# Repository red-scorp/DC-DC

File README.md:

```
 ____  _____   _ ____  _____    _____           _         _   
|    \|     | / |    \|     |  |  _  |___ ___  |_|___ ___| |_ 
|  |  |   --|/ /|  |  |   --|  |   __|  _| . | | | -_|  _|  _|
|____/|_____|_/ |____/|_____|  |__|  |_| |___|_| |___|___|_|  
                                             |___|
```

# DC/DC project

This project is intended to implement some simple multipurpose DC/DC buck and buck-boost converters from easy available components.
This project also features Excel based component values calculator.

I've stared this project to create stable and high quality DC/DC module for my private projects, covering most common usecases:

- Step-down to most common fixed voltages 3.3V, 5V and 12V up to 5A
- Step-up/down from 1.8V-5.5V to 3.3V and 5V up to 3A
- Step-up/down from 2.5V-12V to 3.3V and 5V up to 1A

## DCDC-12V5V5A

**DCDC-12V5V5A** is simple DC/DC step-down converter with fixed output 5V.
When used for more than 1A current it's recommended to glue a heat sink about 20x20mm in a middle of the bottom side of the board.

Preview:

[Schematics in PDF format](doc/DCDC-12V5V5A.pdf)

Features:

- Input: **12V (7V-24V)**
- Output: **5V**
- Current: **5A (peak 10A)**
- Switching: **500kHz**
- Efficiency: **up to 90%**
- Board size: **40x24mm**
- Based on: **Ti LM3150**

CAM files are available.
BoM and PnP files for JLCPCB are available.

## DCDC-12V3V5A

**DCDC-12V3V5A** is simple DC/DC step-down converter with fixed output 3.3V.
When used for more than 1A current it's recommended to glue a heat sink about 20x20mm in a middle of the bottom side of the board.

Preview:

[Schematics in PDF format](doc/DCDC-12V3V5A.pdf)

Features:

- Input: **12V (5V-24V)**
- Output: **3.3V**
- Current: **5A (peak 10A)**
- Switching: **600kHz**
- Efficiency: **up to 90%**
- Board size: **40x24mm**
- Based on: **Ti LM3150**

CAM files are available.
BoM and PnP files for JLCPCB are available.

## DCDC-18V12V5A

**DCDC-18V12V5A** is simple DC/DC step-down converter with fixed output 12V.
When used for more than 1A current it's recommended to glue a heat sink about 20x20mm in a middle of the bottom side of the board.

Preview:

[Schematics in PDF format](doc/DCDC-18V12V5A.pdf)

Features:

- Input: **18V (14V-24V)**
- Output: **12V**
- Current: **5A (peak 10A)**
- Switching: **500kHz**
- Efficiency: **up to 90%**
- Board size: **40x24mm**
- Based on: **Ti LM3150**

CAM files are available.
BoM and PnP files for JLCPCB are available.

## DCDC-18VXV5A

**DCDC-18VXV5A** is simple DC/DC step-down converter with selectable output 2-12V.
When used for more than 1A current it's recommended to glue a heat sink about 20x20mm in a middle of the bottom side of the board.

Preview:

[Schematics in PDF format](doc/DCDC-18VXV5A.pdf)

Features:

- Input: **18V (5V-24V)**
- Output: **2-12V**
- Current: **5A (peak 10A)**
- Switching: **500kHz**
- Efficiency: **up to 90%**
- Board size: **40x24mm**
- Based on: **Ti LM3150**

CAM files are available.
BoM and PnP files for JLCPCB are available.

## DCDC-5V5V3A

**DCDC-5V5V3A** is simple DC/DC step-up/down converter with selectable fixed output 3.3/5V.
When used for more than 1A current it's recommended to glue a heat sink about 20x20mm in a middle of the bottom side of the board.

Preview:

[Schematics in PDF format](doc/DCDC-5V5V3A.pdf)

Features:

- Input: **1.8-5.5V**
- Output: **3.3/5V (select)**
- Current: **3A (peak 5A)**
- Switching: **2.4MHz**
- Efficiency: **up to 90%**
- Board size: **40x24mm**
- Based on: **Ti TPS63020**

CAM files are available.
BoM and PnP files for JLCPCB are available.

## DCDC-5VXV3A

**DCDC-5VXV3A** is simple DC/DC step-up/down converter with selectable output 1.2-5V.
When used for more than 1A current it's recommended to glue a heat sink about 20x20mm in a middle of the bottom side of the board.

Preview:

[Schematics in PDF format](doc/DCDC-5VXV3A.pdf)

Features:

- Input: **1.8-5.5V**
- Output: **1.2-5V**
- Current: **3A (peak 5A)**
- Switching: **2.4MHz**
- Efficiency: **up to 90%**
- Board size: **40x24mm**
- Based on: **Ti TPS63020**

CAM files are available.
BoM and PnP files for JLCPCB are available.

## DCDC-12V5V1A

**DCDC-12V5V1A** is simple DC/DC step-up/down converter with selectable fixed output 3.3/5V.
When used for more than 1A current it's recommended to glue a heat sink about 20x20mm in a middle of the bottom side of the board.

Preview:

[Schematics in PDF format](doc/DCDC-12V5V1A.pdf)

Features:

- Input: **2.5-12V**
- Output: **3.3/5V (select)**
- Current: **1A (peak 2A)**
- Switching: **2.4MHz**
- Efficiency: **up to 90%**
- Board size: **40x24mm**
- Based on: **Ti TPS63060**

CAM files are available.
BoM and PnP files for JLCPCB are available.

## DCDC-BASE-X2A

**DCDC-BASE-X2A** is base board for 2 DC/DC modules with common input and two separate outputs.
When used for more than 1A current it's recommended to glue a heat sinks about 20x20mm in a middle of the bottom side of DCDC boards before soldering them to the base board.

Preview:

[Schematics in PDF format](doc/DCDC-BASE-X2A.pdf)

Features:

- Fits two compatible DCDC modules
- Common/single input
- Two separate outputs
- Compatible with heat sinks up to 24x24mm
- Supports direct and/or hole through soldering of DCDC modules

CAM files are available.

## DCDC-BASE-X2B

**DCDC-BASE-X2B** is base board for 2 DC/DC modules with common input and two separate outputs.
When used for more than 1A current it's recommended to glue a heat sinks about 20x20mm in a middle of the bottom side of DCDC boards before soldering them to the base board.

Preview:

[Schematics in PDF format](doc/DCDC-BASE-X2B.pdf)

Features:

- Fits two compatible DCDC modules
- Common/single input
- Two separate outputs
- Compatible with heat sinks up to 24x24mm
- Supports direct and/or hole through soldering of DCDC modules

CAM files are available.

## DCDC-BOX

**DCDC-BOX** is a enclosure for a single DCDC module, suitable for FDM and SLA 3D printing.

STL file is available.

## DCDC-BOX-X2

**DCDC-BOX-X2** is a enclosure for a X2A and X2B base boards, suitable for FDM and SLA 3D printing.

STL file is available.

## Links

- Interesting paper from Ti [Under the hood of a noninverting buck-boost converter](https://www.ti.com/seclit/ml/slup346/slup346.pdf)
- Product page of [Ti LM3150](https://www.ti.com/product/LM3150)
- Product page of [Ti TPS63020](https://www.ti.com/product/TPS63020)
- Product page of [Ti TPS63060](https://www.ti.com/product/TPS63060)

## How to help

Your contributions as code, resources, or finances are welcome! Please contact me directly via email at andriy.golovnya@gmail.com or through my [GitHub profile](https://github.com/red-scorp).

If you'd like to make a financial contribution, you can donate via [PayPal](http://paypal.me/redscorp) or [Ko-Fi](http://ko-fi.com/redscorp). Your support is greatly appreciated.

Thanks in advance!

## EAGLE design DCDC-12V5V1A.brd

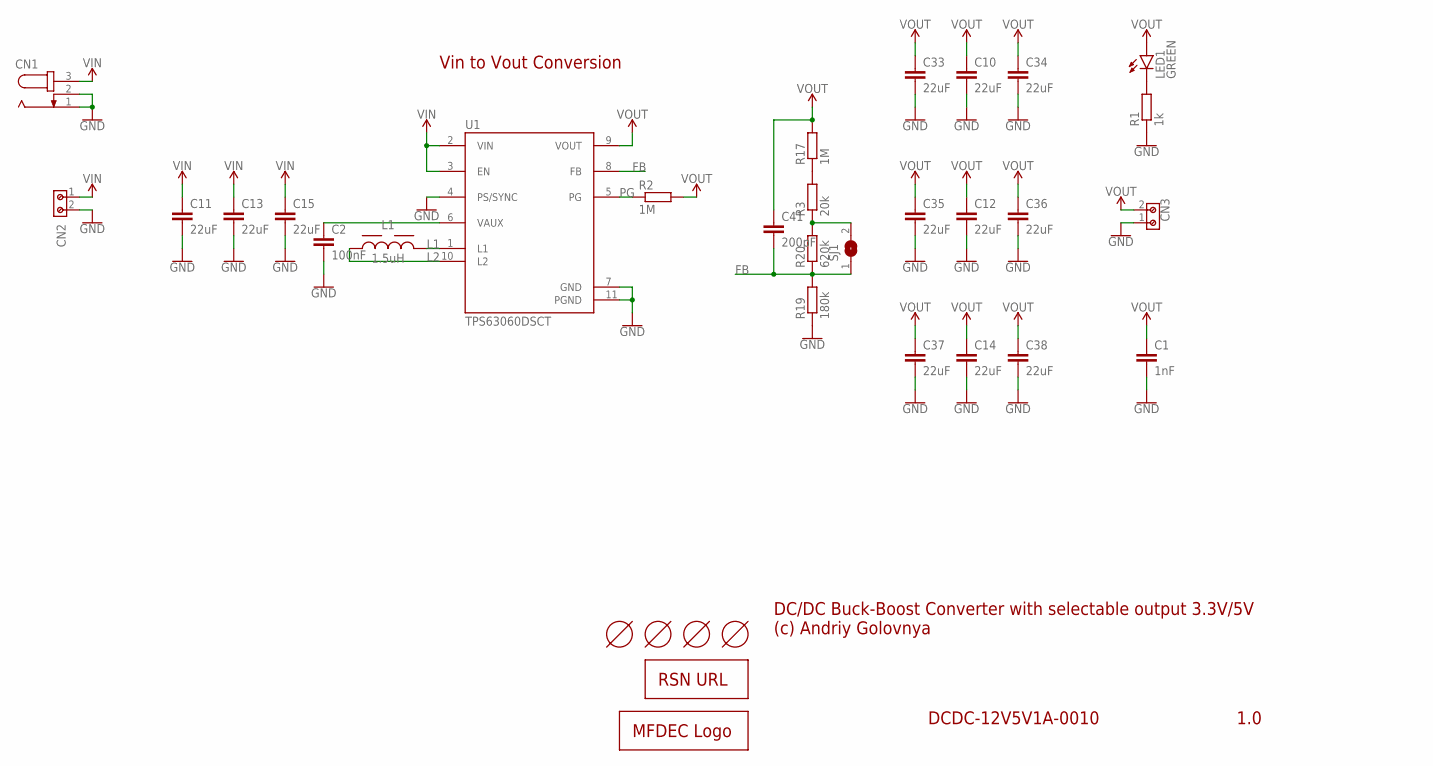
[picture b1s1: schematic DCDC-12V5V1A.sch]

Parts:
C1: 1nF; C0603K
C2: 100nF; C0603K
C10, C11, C12, C13, C14, C15, C33, C34, C35, C36, C37, C38: 22uF; C0805K
C41: 200pF; C0603K
CN1: JACK-PLUG1; SPC4078
CN2, CN3: 691213510002
HOLE1, HOLE2, HOLE3, HOLE4: TOOLINGHOLE; TOOLING-HOLE
L1: 1.5uH; WE-LQS_4018
LED1: GREEN; SML0603
LOGO1: RSNURL_QR_8MM
LOGO2: MFDECLOGO_L_10MM; MFDEC_L_10MM
R1: 1k; R0603
R2, R17: 1M; R0603
R3: 20k; R0603
R19: 180k; R0603
R20: 620k; R0603
SJ1: SJ
U1: TPS63060DSCT; CONV_TPS63060DSCT

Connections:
FB: C41.2, R19.2, R20.1, SJ1.1, U1.8 (FB)
GND: C1.2, C2.2, C10.2, C11.2, C12.2, C13.2, C14.2, C15.2, C33.2, C34.2, C35.2, C36.2, C37.2, C38.2, CN1.1, CN1.2, CN2.2, CN3.1, R1.1, R19.1, U1.4 (PS/SYNC), U1.7 (GND), U1.11 (PGND)
L1: L1.2, U1.1 (L1)
L2: L1.1, U1.10 (L2)
unnamed: LED1.C, R1.2
unnamed: R3.2, R17.1
unnamed: R3.1, R20.2, SJ1.2
PG: R2.1, U1.5 (PG)
VIN: C11.1, C13.1, C15.1, CN1.3, CN2.1, U1.2 (VIN), U1.3 (EN)
VINA: C2.1, U1.6 (VAUX)
VOUT: C1.1, C10.1, C12.1, C14.1, C33.1, C34.1, C35.1, C36.1, C37.1, C38.1, C41.1, CN3.2, LED1.A, R2.2, R17.2, U1.9 (VOUT)

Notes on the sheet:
1.0
DCDC-12V5V1A-0010
DC/DC Buck-Boost Converter with selectable output 3.3V/5V (c) Andriy Golovnya
Vin to Vout Conversion

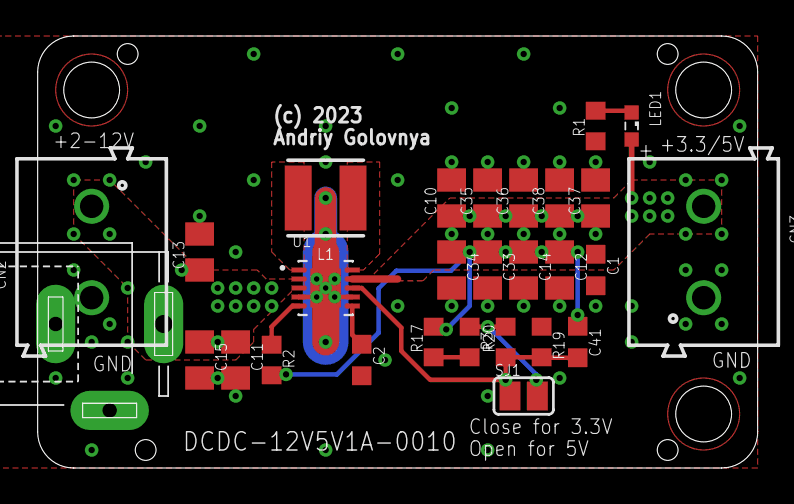
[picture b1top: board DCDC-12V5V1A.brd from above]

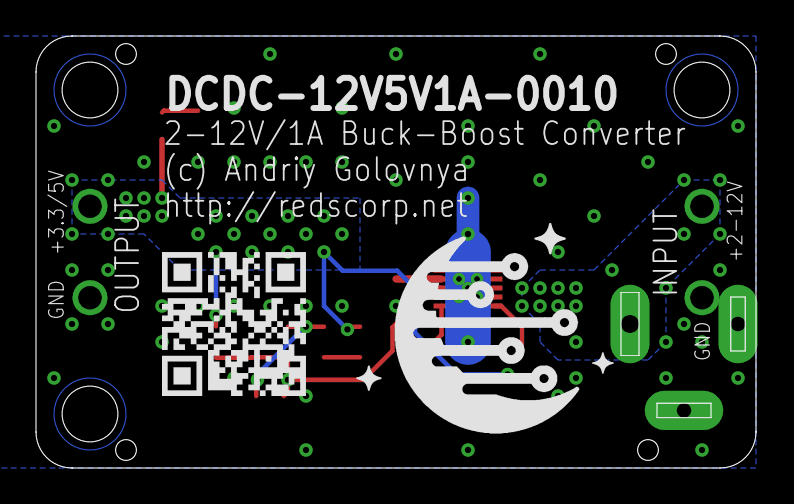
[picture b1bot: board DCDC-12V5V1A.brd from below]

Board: 2 copper layers, 40.0 x 24.0 mm, 34 parts (2 on the bottom side), 11 nets.

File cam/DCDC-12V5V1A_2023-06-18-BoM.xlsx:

Qty | Designator | Footprint | Comment | JLCPCB Part # | Description
1 | C2 | 0603 | 100nF | C14663 | CAPACITOR, European symbol
1 | R19 | 0603 | 180k | C22827 | RESISTOR, European symbol
2 | R2, R17 | 0603 | 1M | C22935 | RESISTOR, European symbol
1 | R1 | 0603 | 1k | C21190 | RESISTOR, European symbol
1 | C1 | 0603 | 1nF | C1588 | CAPACITOR, European symbol
1 | L1 | SMD | 1.5uH | C354573 | WE-LQS SMD Power Inductor
1 | C41 | 0603 | 200pF | C1600 | CAPACITOR, European symbol
1 | R3 | 0603 | 20k | C4184 | RESISTOR, European symbol
12 | C10, C11, C12, C13, C14, C15, C33, C34, C35, C36, C37, C38 | 0805 | 22uF | C45783 | CAPACITOR, European symbol
1 | R20 | 0603 | 620k | C23219 | RESISTOR, European symbol
1 | LED1 | 0603 | GREEN | C72043 | LED
1 | U1 | WSON-10-EP(3x3) | TPS63060DSCR | C48567 | Buck-boost type Adjustable 2.5V~8V 2A 2.5V~12V DFN-10-EP(3x3) DC-DC Converters 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

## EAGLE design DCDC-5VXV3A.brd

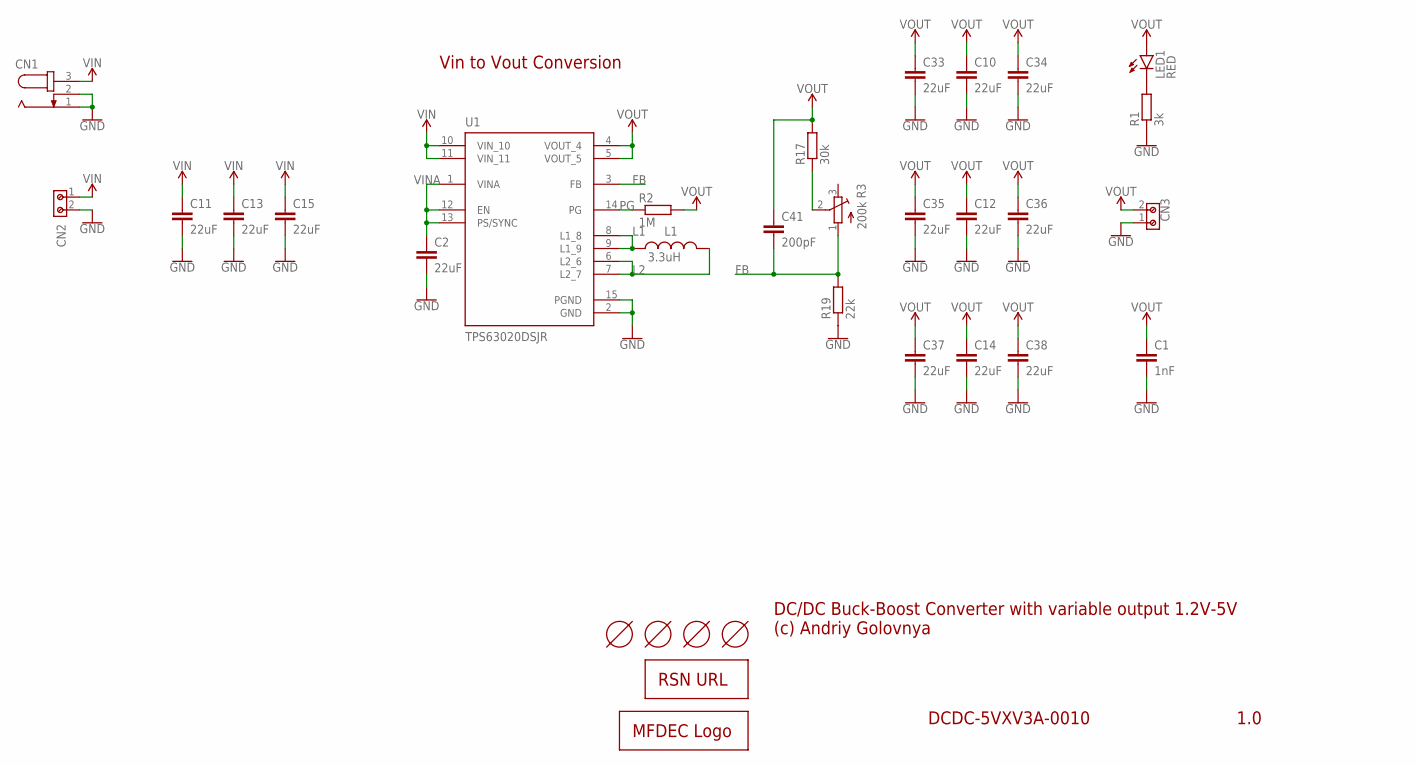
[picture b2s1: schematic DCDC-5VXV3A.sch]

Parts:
C1: 1nF; C0603K
C2, C10, C11, C12, C13, C14, C15, C33, C34, C35, C36, C37, C38: 22uF; C0805K
C41: 200pF; C0603K
CN1: JACK-PLUG1; SPC4078
CN2, CN3: 691213510002
HOLE1, HOLE2, HOLE3, HOLE4: TOOLINGHOLE; TOOLING-HOLE
L1: 3.3uH; WE-CHSA_1011
LED1: RED; SML0603
LOGO1: RSNURL_QR_8MM
LOGO2: MFDECLOGO_L_10MM; MFDEC_L_10MM
R1: 3k; R0603
R2: 1M; R0603
R3: 200k; TC33X
R17: 30k; R0603
R19: 22k; R0603
U1: TPS63020DSJR; IC_TPS63020DSJR

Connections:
FB: C41.2, R3.1 (A), R19.2, U1.3 (FB)
GND: C1.2, C2.2, C10.2, C11.2, C12.2, C13.2, C14.2, C15.2, C33.2, C34.2, C35.2, C36.2, C37.2, C38.2, CN1.1, CN1.2, CN2.2, CN3.1, R1.1, R19.1, U1.2 (GND), U1.15 (PGND)
L1: L1.1, U1.8 (L1_8), U1.9 (L1_9)
L2: L1.2, U1.6 (L2_6), U1.7 (L2_7)
unnamed: LED1.C, R1.2
unnamed: R3.2 (S), R17.1
PG: R2.1, U1.14 (PG)
VIN: C11.1, C13.1, C15.1, CN1.3, CN2.1, U1.10 (VIN_10), U1.11 (VIN_11)
VINA: C2.1, U1.1 (VINA), U1.12 (EN), U1.13 (PS/SYNC)
VOUT: C1.1, C10.1, C12.1, C14.1, C33.1, C34.1, C35.1, C36.1, C37.1, C38.1, C41.1, CN3.2, LED1.A, R2.2, R17.2, U1.4 (VOUT_4), U1.5 (VOUT_5)

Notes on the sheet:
1.0
DCDC-5VXV3A-0010
DC/DC Buck-Boost Converter with variable output 1.2V-5V (c) Andriy Golovnya
Vin to Vout Conversion

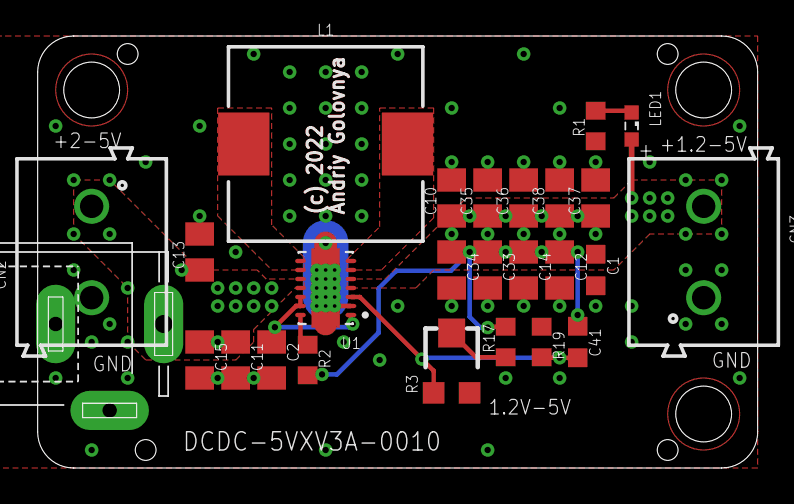
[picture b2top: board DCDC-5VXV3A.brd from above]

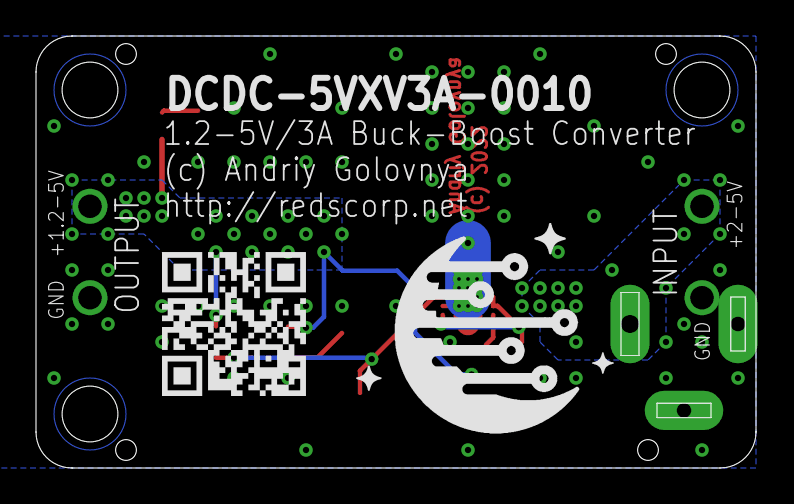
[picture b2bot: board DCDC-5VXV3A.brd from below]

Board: 2 copper layers, 40.0 x 24.0 mm, 32 parts (2 on the bottom side), 10 nets.

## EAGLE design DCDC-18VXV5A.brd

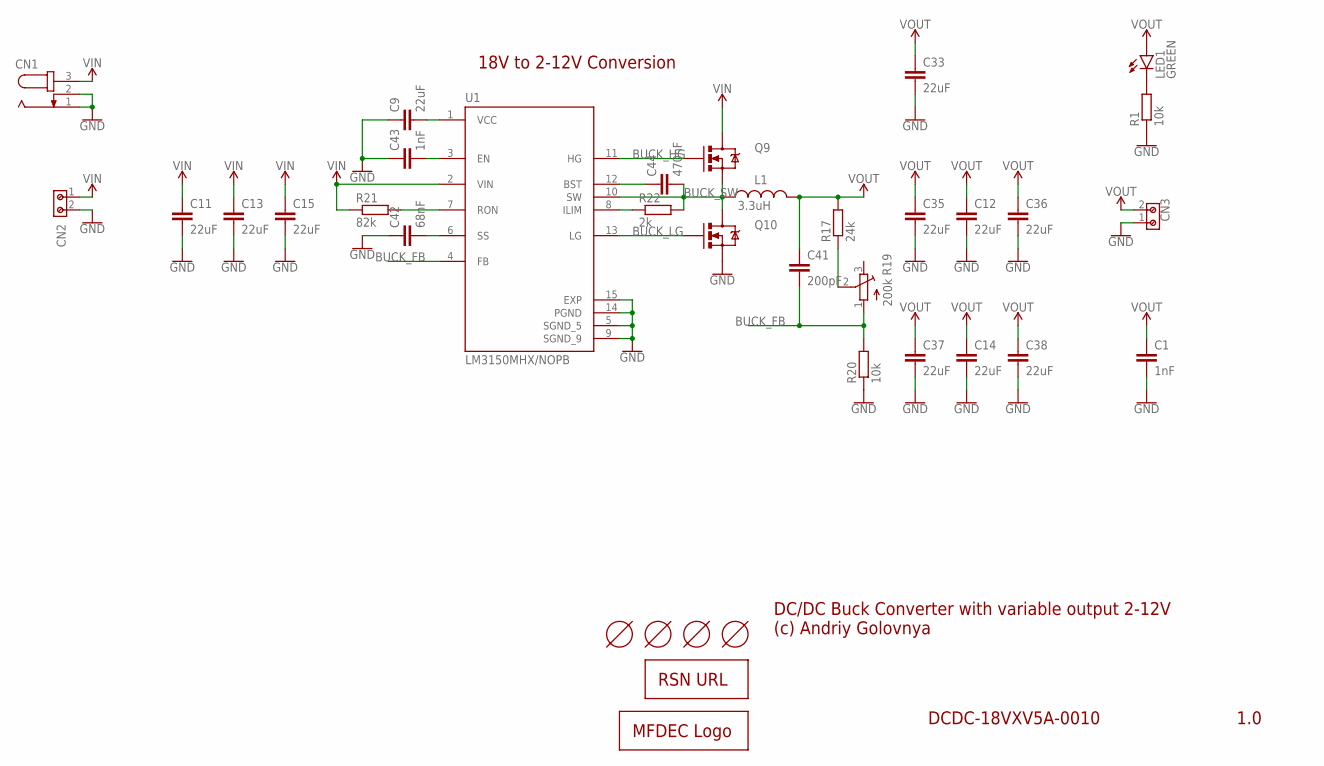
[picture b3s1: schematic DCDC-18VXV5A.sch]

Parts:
C1, C43: 1nF; C0603K
C9, C11, C12, C13, C14, C15, C33, C35, C36, C37, C38: 22uF; C0805K
C41: 200pF; C0603K
C42: 68nF; C0603K
C44: 470nF; C0603K
CN1: JACK-PLUG1; SPC4078
CN2, CN3: 691213510002
HOLE1, HOLE2, HOLE3, HOLE4: TOOLINGHOLE; TOOLING-HOLE
L1: 3.3uH; WE-CHSA_1011
LED1: GREEN; SML0603
LOGO1: RSNURL_QR_8MM
LOGO2: MFDECLOGO_L_10MM; MFDEC_L_10MM
Q9, Q10: NMOSFET; DPAK
R1, R20: 10k; R0603
R17: 24k; R0603
R19: 200k; TC33X
R21: 82k; R0603
R22: 2k; R0603
U1: LM3150MHX/NOPB; SOP65P640X110-15N

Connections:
BUCK_BST: C44.1, U1.12 (BST)
BUCK_EN: C43.2, U1.3 (EN)
BUCK_FB: C41.2, R19.1 (A), R20.2, U1.4 (FB)
BUCK_HG: Q9.1 (G), U1.11 (HG)
BUCK_ILIM: R22.1, U1.8 (ILIM)
BUCK_LG: Q10.1 (G), U1.13 (LG)
BUCK_RON: R21.2, U1.7 (RON)
BUCK_SS: C42.2, U1.6 (SS)
BUCK_SW: C44.2, L1.1, Q9.3 (S), Q10.4 (D), R22.2, U1.10 (SW)
BUCK_VCC: C9.2, U1.1 (VCC)
GND: C1.2, C9.1, C11.2, C12.2, C13.2, C14.2, C15.2, C33.2, C35.2, C36.2, C37.2, C38.2, C42.1, C43.1, CN1.1, CN1.2, CN2.2, CN3.1, Q10.3 (S), R1.1, R20.1, U1.5 (SGND_5), U1.9 (SGND_9), U1.14 (PGND), U1.15 (EXP)
unnamed: LED1.C, R1.2
unnamed: R17.1, R19.2 (S)
VIN: C11.1, C13.1, C15.1, CN1.3, CN2.1, Q9.4 (D), R21.1, U1.2 (VIN)
VOUT: C1.1, C12.1, C14.1, C33.1, C35.1, C36.1, C37.1, C38.1, C41.1, CN3.2, L1.2, LED1.A, R17.2

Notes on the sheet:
1.0
DCDC-18VXV5A-0010
DC/DC Buck Converter with variable output 2-12V (c) Andriy Golovnya
18V to 2-12V Conversion

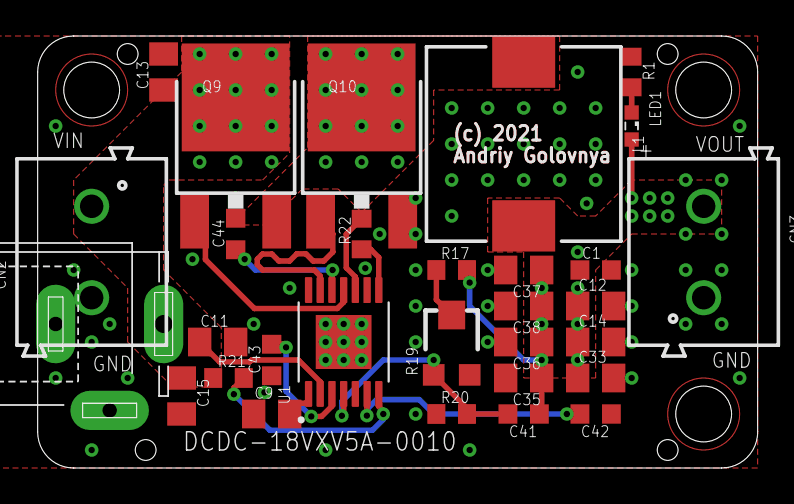
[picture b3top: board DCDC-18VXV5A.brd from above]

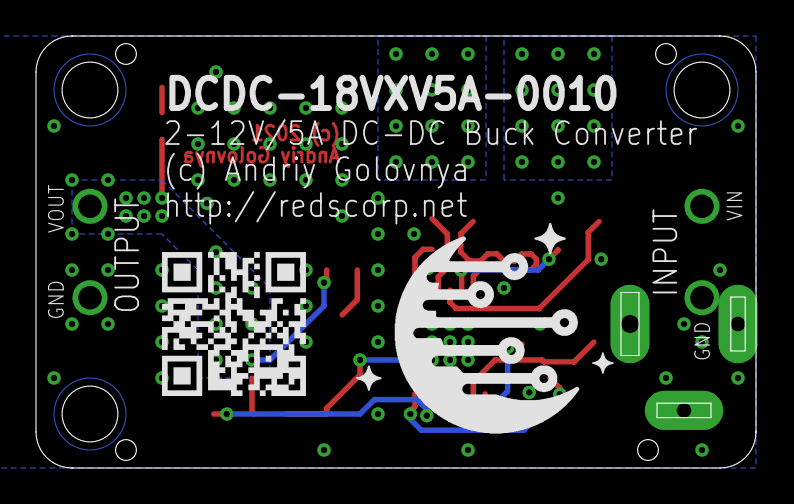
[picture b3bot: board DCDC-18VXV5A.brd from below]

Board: 2 copper layers, 40.0 x 24.0 mm, 36 parts (2 on the bottom side), 15 nets.

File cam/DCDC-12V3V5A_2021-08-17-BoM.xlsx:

Qty | Designator | Footprint | Comment | LCSC Part #
1 | R20 | 0603 | 10k | C25804
1 | C43 | 0603 | 1nF | C1588
1 | C41 | 0603 | 200pF | C1600
13 | C9, C10, C11, C12, C13, C14, C15, C33, C34, C35, C36, C37, C38 | 0805 | 22uF | C45783
2 | R1, R22 | 0603 | 2k | C22975
1 | L1 | IND-SMD | 3.3uH | C241408
1 | R19 | 0603 | 330 | C23138
1 | C44 | 0603 | 470nF | C1623
2 | R17, R21 | 0603 | 47k | C25819
1 | C42 | 0603 | 68nF | C31658
1 | LED1 | LED_0603 | GREEN | C72043
1 | U1 | HTSSOP-14_EP_4.4x5.0x0.65P | LM3150MHX/NOPB | C48112
2 | Q9, Q10 | TO-252-2 | NCE3050K | C127863

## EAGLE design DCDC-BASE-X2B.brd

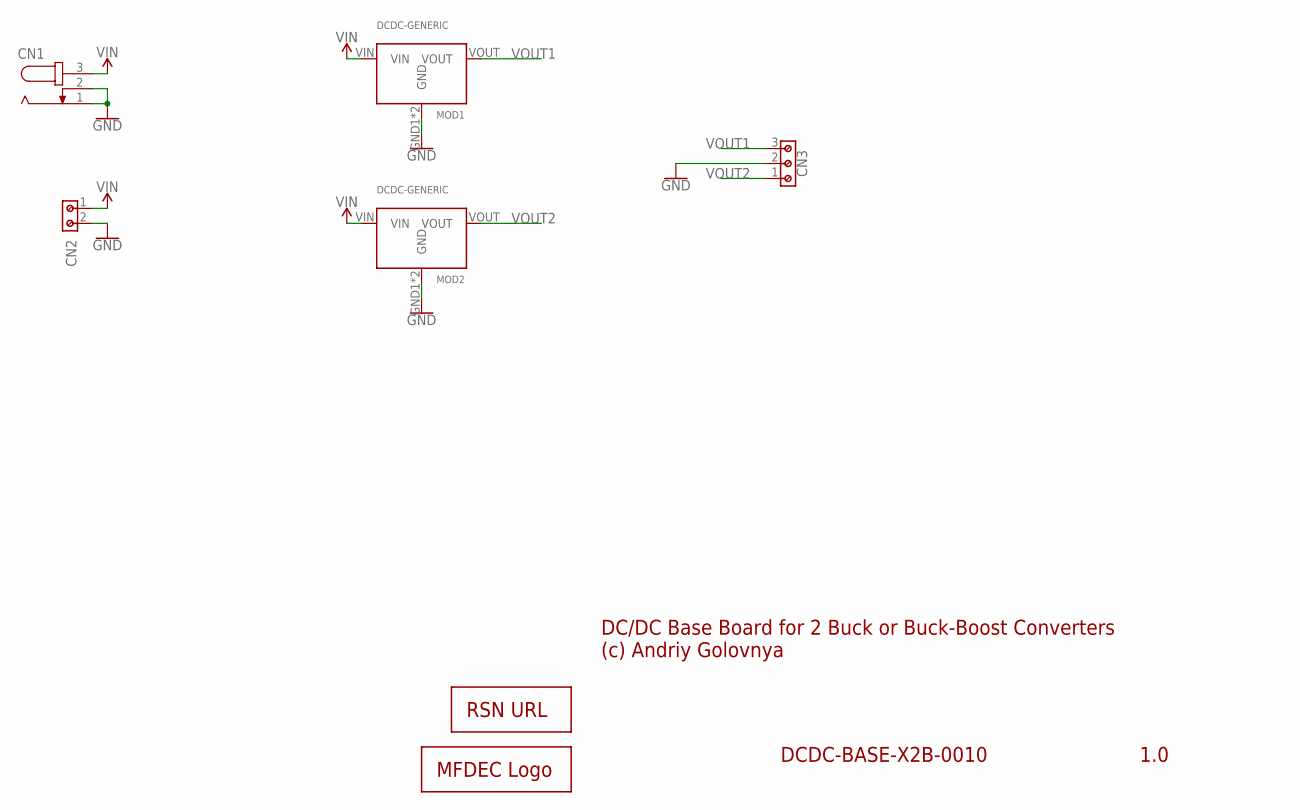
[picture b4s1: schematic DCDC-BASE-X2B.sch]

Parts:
CN1: JACK-PLUG1; SPC4078
CN2: 691213510002
CN3: 691213510003
LOGO1: RSNURL_QR_8MM
LOGO2: MFDECLOGO_L_10MM; MFDEC_L_10MM
MOD1, MOD2: DCDC-GENERIC; DCDC-BOARD

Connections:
GND: CN1.1, CN1.2, CN2.2, CN3.2, MOD1.GND1 (GND), MOD1.GND2 (GND), MOD2.GND1 (GND), MOD2.GND2 (GND)
VIN: CN1.3, CN2.1, MOD1.VIN, MOD2.VIN
VOUT1: CN3.3, MOD1.VOUT
VOUT2: CN3.1, MOD2.VOUT

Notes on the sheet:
1.0
DCDC-BASE-X2B-0010
DC/DC Base Board for 2 Buck or Buck-Boost Converters (c) Andriy Golovnya

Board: 2 copper layers, 7 parts (1 on the bottom side), 4 nets, no tracks yet.

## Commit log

2021-07-24 Add basic schematics of 12V-5V-5A DC-DC buck converter.
2021-07-24 Added board design. Added descriptive texts. Generated CAM files.
2021-07-24 Fixed some placement. Generated CAM files.
2021-07-24 Added BoM and PnP files.
2021-07-25 Exchanged MOSFETs for bigger once. Generated CAM files. Generated BoM and PnP files.
2021-07-25 Added indication LED. Generated CAM files. Generated BoM and PnP files.
2021-07-26 Minor improvements in board routing. Generated CAM files. Fixed footprints in BoM.
2021-07-26 Minor improvements in board routing. Generated CAM files.
2021-08-07 Added tooling holes. Generated CAM files.
2021-08-08 Added copper thermal pads at the back of the board.
2021-08-09 Added more space between fills. Generated CAM files.
2021-08-11 Add few descriptive texts. Generated CAM files.
2021-08-12 Added reference documents.
2021-08-15 Added calculation for 3.3v and 12v buck converters.
2021-08-17 Renamed 12V line to Vin. Generated CAM files.
2021-08-17 Added 3.3V buck board
2021-08-17 Fixed few values on 3.3V schematics. Generated CAM files.
2021-08-17 Text fixed.
2021-08-17 Added 12V buck converter. Generated CAM files.
2021-08-17 Generated BoM and PnP files.
2021-08-17 Generated PDF schematics. Generated PNG preview. Updated descriptions.
2021-08-18 Updated descriptions.
2021-08-20 Added FUNDING file.
2021-08-30 Made new layout of DC-DC board. Improved XLS calculator. Generated CAM files. Generated BoM and PnP files. Generated PNG preview. Generated PDF schematics.
2021-08-30 Improved layout of DC-DC board. Rotated input terminal. Improved XLS calculator. Generated CAM files. Generated BoM and PnP files. Generated PNG preview. Generated PDF schematics.
2021-08-30 Fixed 5V board BoM.
2021-08-30 Improved layout of DC-DC board. Rotated input terminal. Generated CAM files. Generated BoM and PnP files. Generated PNG preview. Generated PDF schematics.
2021-08-30 Fixed text on schematics. Generated PDF schematics. Removed wrongly committed CSV file.
2021-08-31 Added proper voltage symbols on 3.3v and 12v boards. Generated PDF schematics.
2021-09-08 Updated LM3150 PDF.
2021-09-08 Added TPS63020 PDF.
2021-09-09 Added basic voltage divider calculator for TPS63020.
2021-09-09 Added 5V-5V buck-boost board.
2021-09-10 Improved schematics and routing of 5V-5V board. Generated PDF schematics. Generated PNG preview. Generated CAM files.
2021-09-10 Improved routing of 5V-5V board. Generated PNG preview. Generated CAM files.
2021-09-11 Fixed few traces. Generated CAM files. Generated PNG preview.
2021-09-18 Moved some texts and tooling holes a bit. Generated CAM files. Generated PNG preview. Generated PDF schematics. Renamed BoM and PnP files.
2021-09-19 Fixed typo
2021-09-21 Update DESCRIPTION
2021-09-21 Added 200k resistor to improve voltage output. Generated CAM files. Generated PNG preview. Generated PDF schematics. Adjusted BoM and PnP files. Adjusted Excel calculator.
2021-09-21 Fixed typo. Generated PDF schematics.
2021-09-21 Fixed PnP file.
2021-09-21 Changed font size. Generated CAM files. Generated PNG preview.
2021-09-21 Updated DESCRIPTION
2021-09-21 fixed schematics description. Generated PDF schematics.
2021-09-22 Added x2 base board. Generated CAM files. Generated PNG preview. Generated PDF schematics.
2021-09-23 Small fixes. Generated PNG preview. Generated CAM files.
2021-09-23 Added 3d enclosure. Generated STL model. Updated README.
2021-09-23 Generated PNG preview. Updated README.
2021-09-24 Added few texts. Generated PNG preview. Generated CAM files.
2021-09-25 Renamed X2 board to X2A. Generated CAM files. Generated PNG preview. Generated PDF schematics. Updated descriptions.
2021-09-25 Added x2B board. Generated CAM files. Generated PNG preview. Generated PDF schematics. Updated description.
2021-09-25 Added x2 box 3d model. Generated STL model. Generated PNG preview. Updated description.
2021-09-26 Added few vias. Generated CAM files. Generated PNG preview. Renamed BoM and PnP files.
2021-09-30 Moved some stuff around on x2 boards. Generated CAM files. Generated PNG preview.
2021-10-03 Added variable version of buck converter board. Generated PNG preview. Generated PDF schematics.
2021-10-05 Changed LEDs resistor. Generated CAM filers. Generated PNG preview. Generated PDF schematics. Updated description.
2021-10-06 Added board name to the top of the board too. Generated CAM files. Generated PNG preview.
2021-10-07 Renamed 17V boards to 18V. No other changes are made.
2021-10-07 Changed texts on 18V-12V boards. Generated CAM files. Generated PNG preview. Generated PDF schematics.
2021-10-08 Renamed VOUT line. Generated CAM files. Generated PNG preview. Generated PDF schematics.
2021-10-10 Generated BoM and PnP files for 18VXV5A board.
2021-10-10 Updated description.
2021-12-04 tree reorganization to cleanup some space.
2022-01-21 Added new step-up/down board. Generated CAM files. Generated PNG preview. Generated PDF schematics. Generated BoM and PnP files. Updated descriptions. Updated XLS calculator.
2022-01-24 Added Ko-Fi link
2022-02-06 Updated descriptions
2023-06-18 Added new 12V5V1A board.
2023-06-18 Generated PDF schematics
2023-06-18 Added copyright message. Generated CAM files. Generated PNG preview.
2023-06-22 Generated BOM and PNP files
2023-06-23 Changed L1 inductor from 1uH to 1.5uH for higher output current stability. Generated PDF schematics. Updated BoM file.
2023-06-25 Rotated U1 to fit in place properly

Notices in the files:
DCDC-12V5V1A.brd:
(c) 2023
DCDC-18VXV5A.brd:
(c) 2021
DCDC-5VXV3A.brd:
(c) 2022
parts and their libraries:
Wurth_Connectors_WR-TBL Rising Cage Clam: Copyright: Würth Elektronik
SparkFun-PowerSymbols: Licensing: Creative Commons ShareAlike 4.0 International - https://creativecommons.org/licenses/by-sa/4.0
